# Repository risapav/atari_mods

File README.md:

# atari_mods
atari st HW modifications and add ones

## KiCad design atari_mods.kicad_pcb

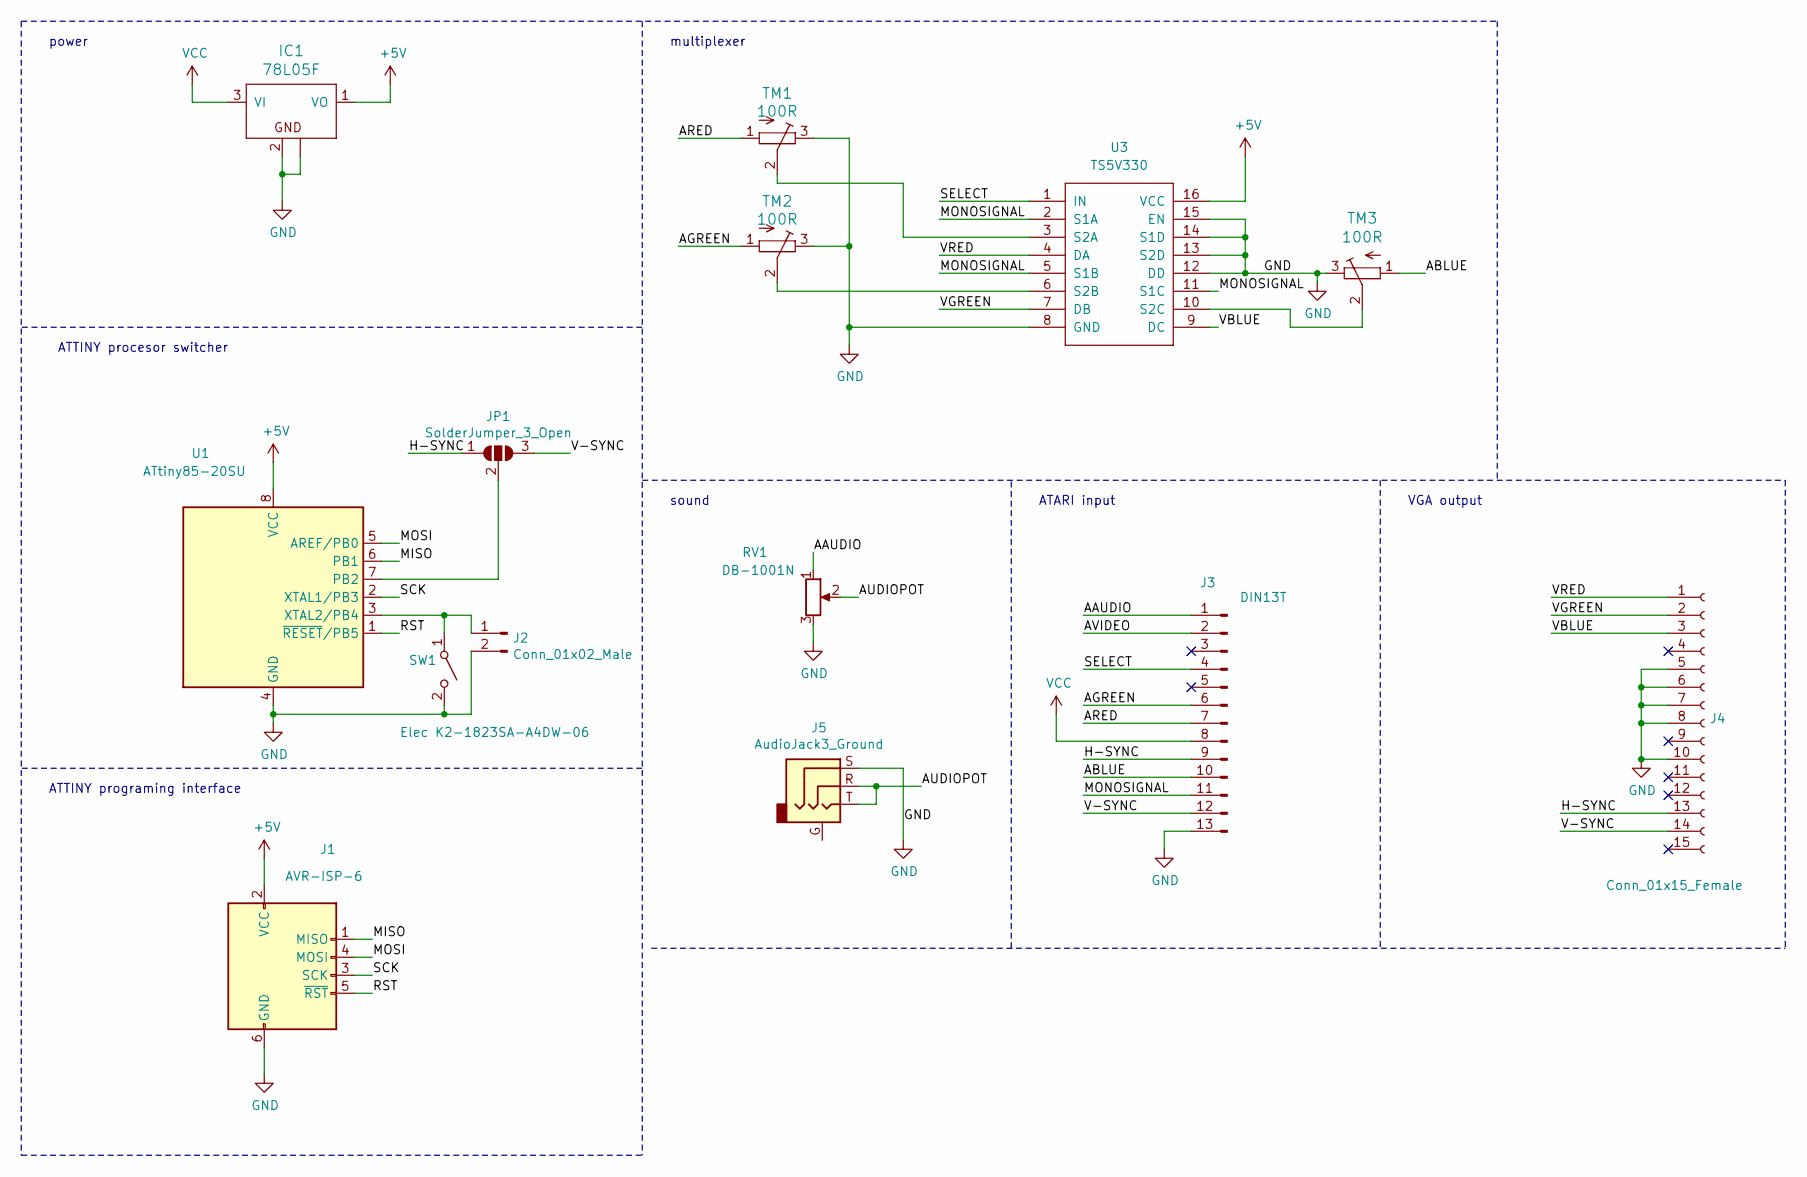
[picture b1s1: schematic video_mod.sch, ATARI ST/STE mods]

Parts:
IC1: 78L05F; SOT-89-3_Handsoldering
J1: AVR-ISP-6; PinHeader_2x03_P1.27mm_Vertical
J2: Conn_01x02_Male; PinHeader_1x02_P1.27mm_Vertical
J3: DIN13T; ADADS
J4: Conn_01x15_Female; DSUB-15-HD_Female_Vertical_P2.29x1.98mm_MountingHoles
J5: AudioJack3_Ground; Jack_3.5mm_Switronic_ST-005-G_horizontal
JP1: SolderJumper_3_Open; SolderJumper-3_P1.3mm_Open_Pad1.0x1.5mm
RV1: DB-1001N; THUMB_POT
SW1: Elec K2-1823SA-A4DW-06; K2-1823SA
TM1, TM2, TM3: 100R; Potentiometer_Bourns_TC33X_Vertical
U1: ATtiny85-20SU; SOIJ-8_5.3x5.3mm_P1.27mm
U3: TS5V330; SOIC-16_4.55x10.3mm_P1.27mm

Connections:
+5V: IC1.1 (VO), J1.2 (VCC), U1.8 (VCC), U3.16 (VCC)
/video_mod/AAUDIO: J3.1, RV1.1
/video_mod/ABLUE: J3.10, TM3.1 (A)
/video_mod/AGREEN: J3.6, TM2.1 (A)
/video_mod/ARED: J3.7, TM1.1 (A)
/video_mod/AUDIOPOT: J5.R, J5.T, RV1.2
/video_mod/AVIDEO: J3.2
/video_mod/H-SYNC: J3.9, J4.13, JP1.1 (A)
/video_mod/MISO: J1.1 (MISO), U1.6 (PB1)
/video_mod/MONOSIGNAL: J3.11, U3.2 (S1A), U3.5 (S1B), U3.11 (S1C)
/video_mod/MOSI: J1.4 (MOSI), U1.5 (AREF/PB0)
/video_mod/RST: J1.5 (~RST), U1.1 (~RESET~/PB5)
/video_mod/SCK: J1.3 (SCK), U1.2 (XTAL1/PB3)
/video_mod/SELECT: J3.4, U3.1 (IN)
/video_mod/V-SYNC: J3.12, J4.14, JP1.3 (B)
/video_mod/VBLUE: J4.3, U3.9 (DC)
/video_mod/VGREEN: J4.2, U3.7 (DB)
/video_mod/VRED: J4.1, U3.4 (DA)
GND: IC1.2 (GND), IC1.2@1 (GND@1), J1.6 (GND), J2.2, J3.13, J4.5, J4.6, J4.7, J4.8, J4.10, J5.S, RV1.3, SW1.2 (B), TM1.3 (E), TM2.3 (E), TM3.3 (E), U1.4 (GND), U3.8 (GND), U3.12 (DD), U3.13 (S2D), U3.14 (S1D), U3.15 (EN)
unnamed: J2.1, SW1.1 (A), U1.3 (XTAL2/PB4)
unnamed: JP1.2 (C), U1.7 (PB2)
unnamed: TM1.2 (S), U3.3 (S2A)
unnamed: TM2.2 (S), U3.6 (S2B)
unnamed: TM3.2 (S), U3.10 (S2C)
VCC: IC1.3 (VI), J3.8

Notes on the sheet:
ATTINY programing interface
ATTINY procesor switcher
power
sound
multiplexer
VGA output
ATARI input

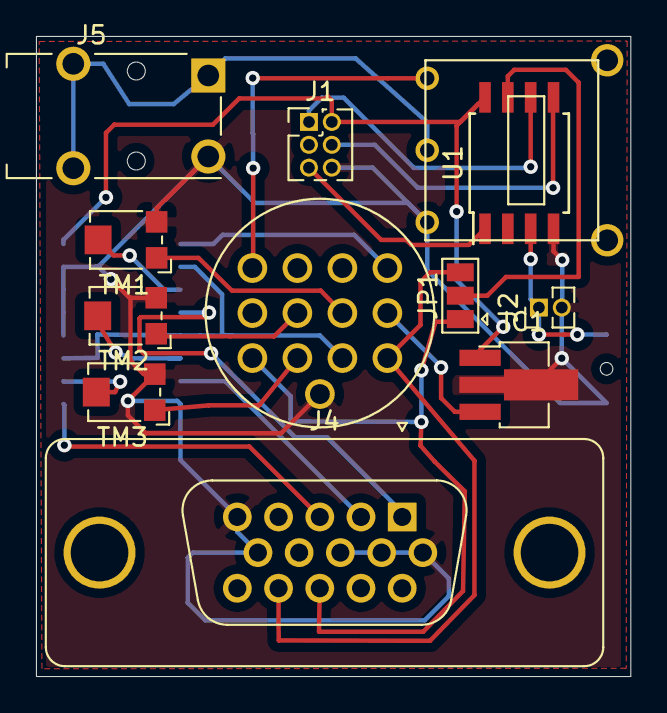
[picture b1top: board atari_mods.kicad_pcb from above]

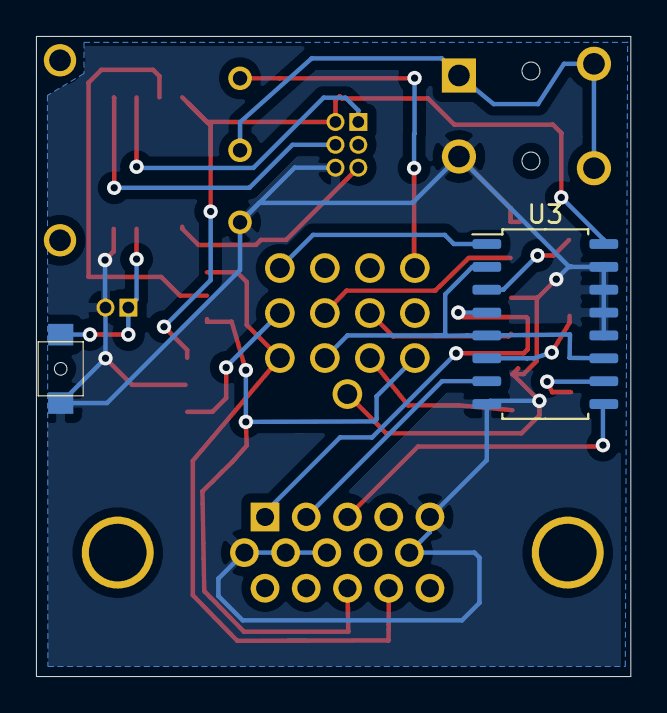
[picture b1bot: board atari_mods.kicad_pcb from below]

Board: 2 copper layers, 33.0 x 35.6 mm, 14 parts (2 on the bottom side), 24 nets.
